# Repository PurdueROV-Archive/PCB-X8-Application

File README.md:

# PCB-X8-Application
The board that contains mission specific electronics

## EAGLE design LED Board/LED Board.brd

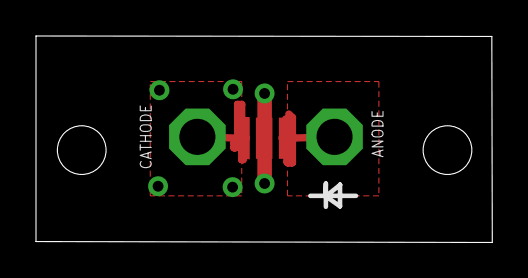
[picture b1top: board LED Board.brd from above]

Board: 2 copper layers, 25.3 x 11.5 mm, 3 parts (0 on the bottom side), 2 nets.

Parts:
ANODE: PTR1PAD1-20; P1-20
CATHODE: PTR1PAD1-20; P1-20
D1: CREE; CREE-XLAMP-XM-L

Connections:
CAM_LEDV: ANODE.TP, D1.A, D1.A@1
GND: CATHODE.TP, D1.C, D1.C1, D1.C@1

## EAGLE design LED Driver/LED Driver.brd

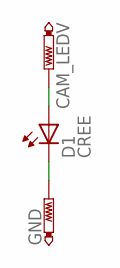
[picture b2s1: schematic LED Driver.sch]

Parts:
CAM_LEDV: PTR1PAD1-20; P1-20
D1: CREE; CREE-XLAMP-XM-L
GND: PTR1PAD1-20; P1-20

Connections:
CAM_LEDV: CAM_LEDV.TP, D1.A, D1.A@1 (A)
GND: D1.C, D1.C1 (C), D1.C@1 (C), GND.TP

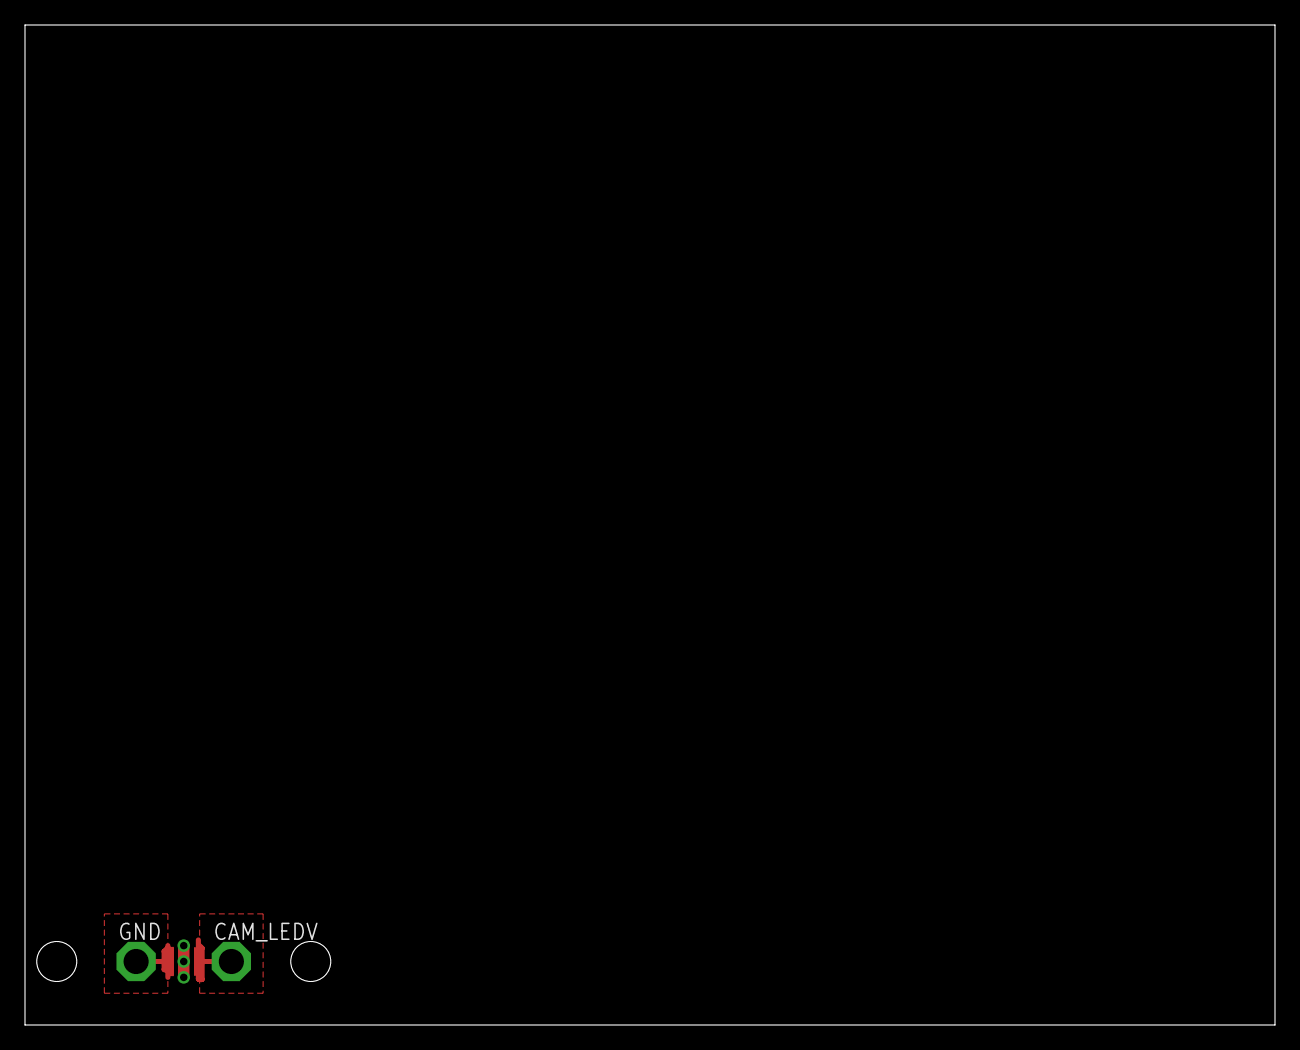
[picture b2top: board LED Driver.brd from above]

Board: 2 copper layers, 100.0 x 80.0 mm, 3 parts (0 on the bottom side), 2 nets.

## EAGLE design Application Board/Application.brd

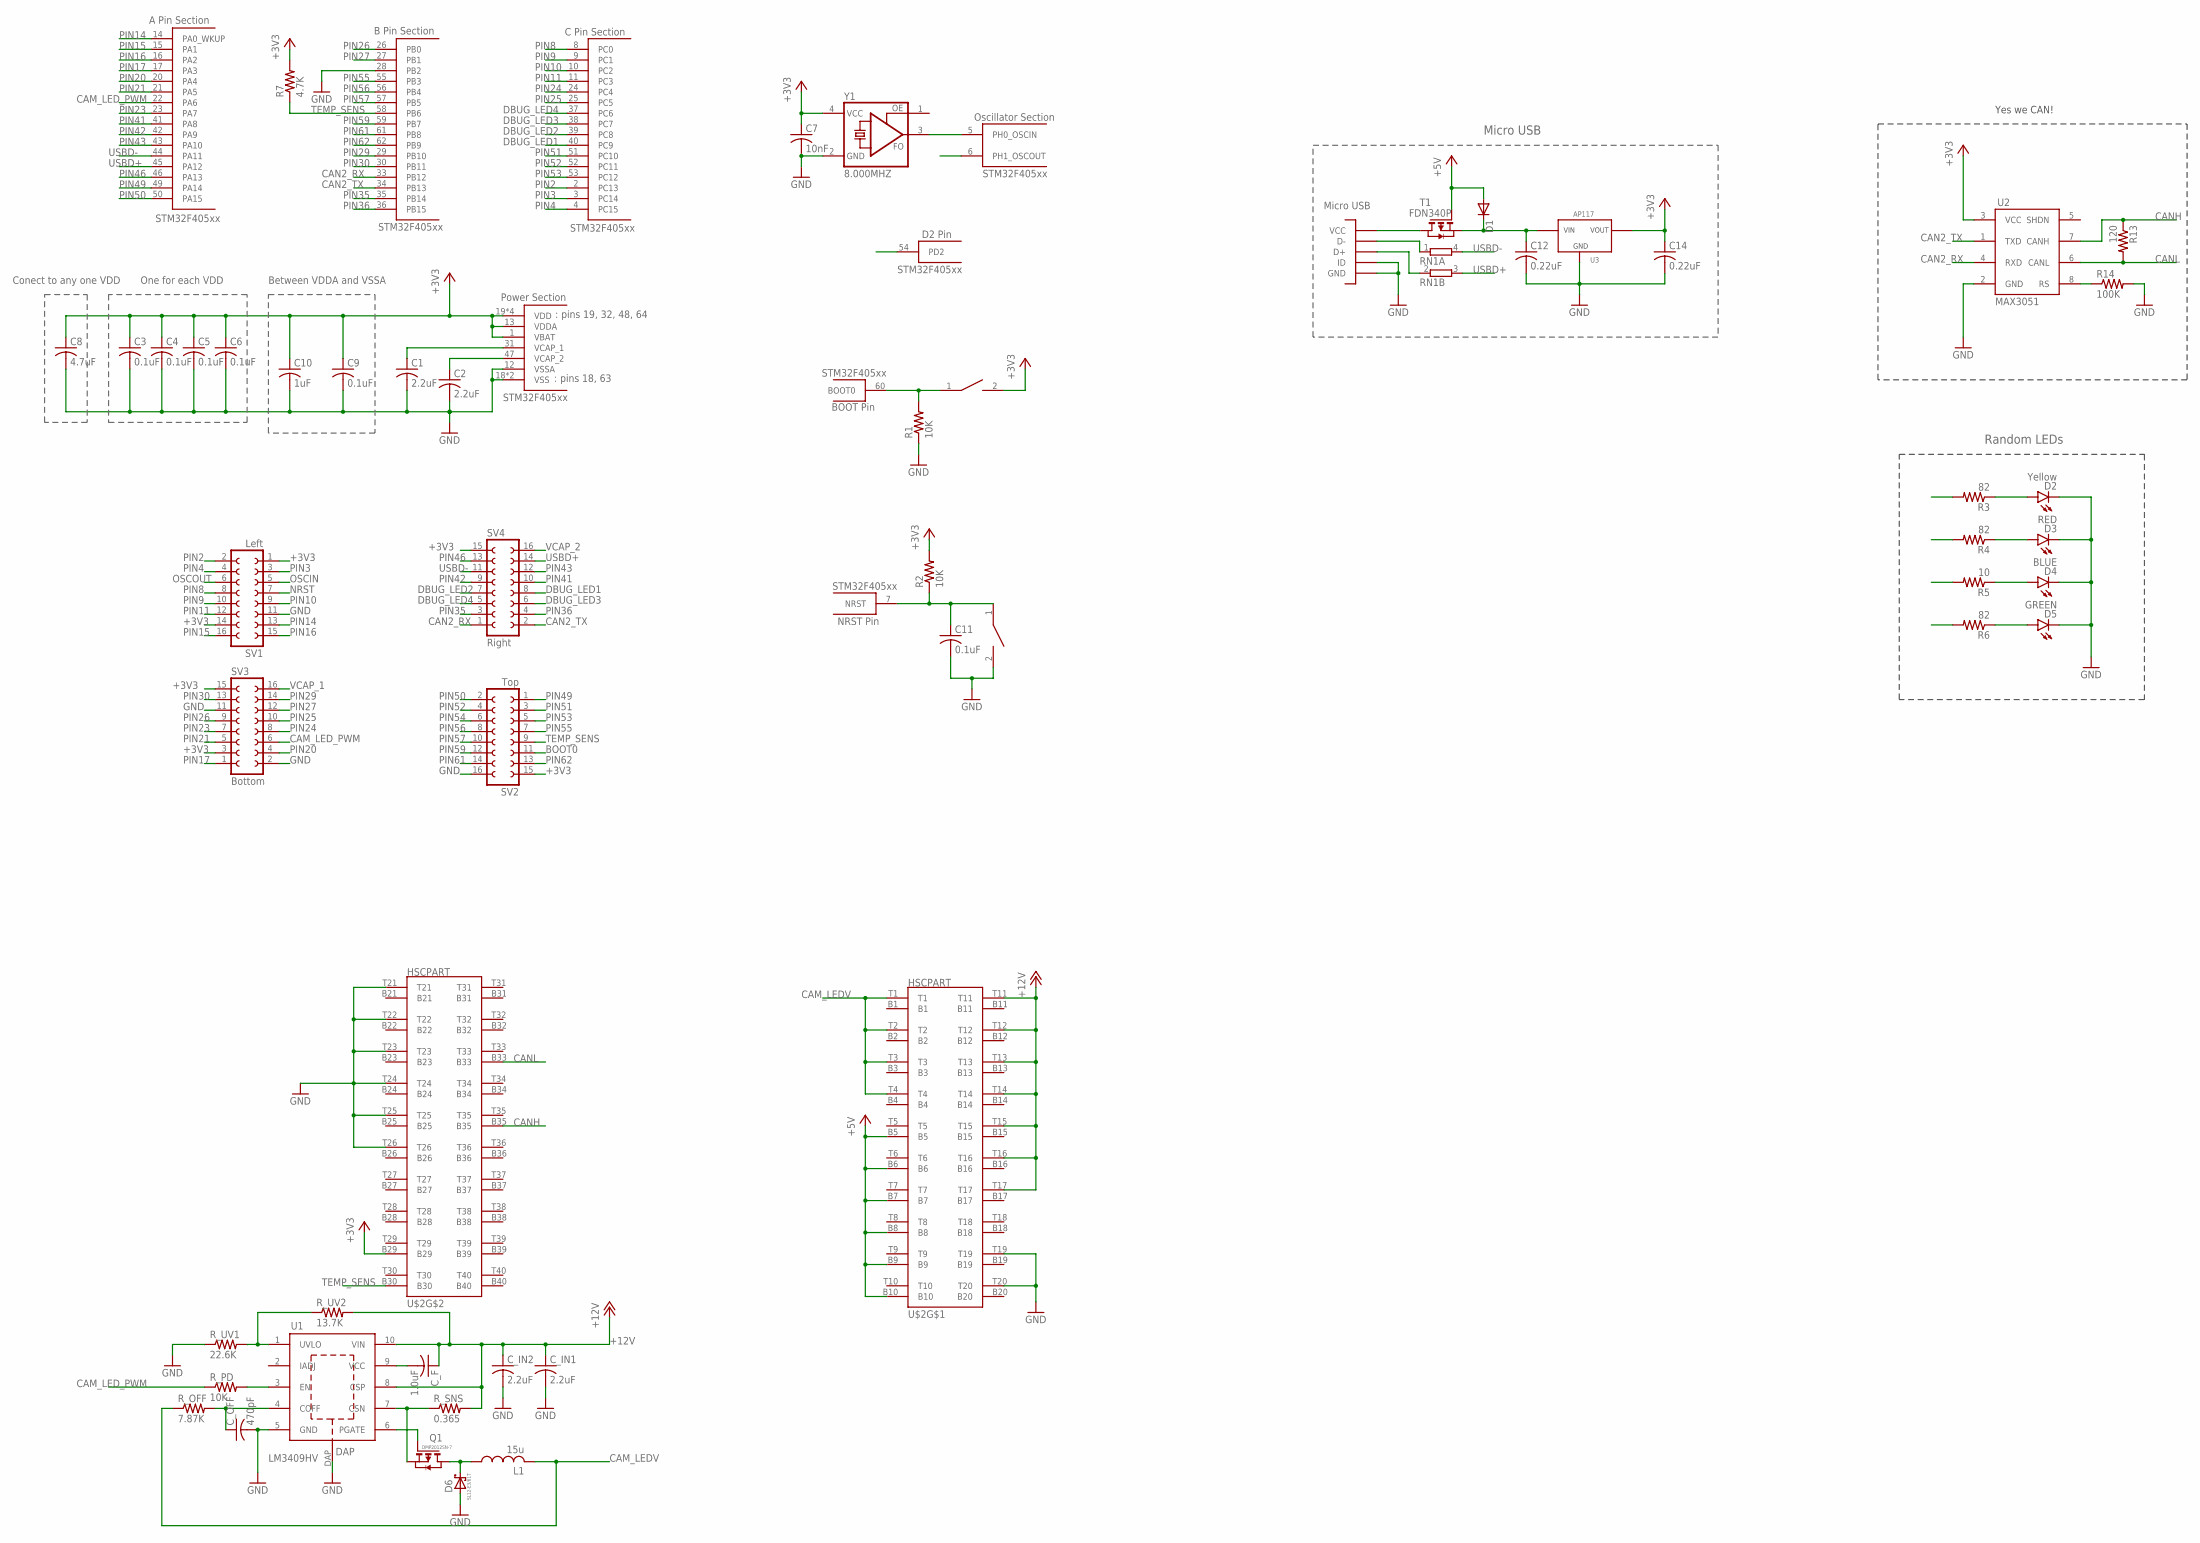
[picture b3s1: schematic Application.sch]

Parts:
C1, C2: 2.2uF; C0603
C3, C4, C5, C6, C9, C11: 0.1uF; C0603
C7: 10nF; C0603
C8: 4.7uF; C0603
C10: 1uF; C0603
C12, C14: 0.22uF; C0603
C_F: 1.0uF; C0603
C_IN1, C_IN2: 2.2uF; C0603
C_OFF: 470pF; C0603
D1: DIODE-DO-214AC; DO-214AC
D2: Yellow; LED-0603
D3: RED; LED-0603
D4: BLUE; LED-0603
D5: GREEN; LED-0603
D6: SL12-E3/61T
L1: 15u; SRN8040
Q1: DMP2012SN-7
R1, R2: 10K; R0603
R3, R4, R6: 82; R0603
R5: 10; R0603
R7: 4.7K; R0603
R13: 120; R0603
R14: 100K; R0603
RN1: 2R-NEXBV4V; EXBV4V
R_OFF: 7.87K; R0603
R_PD: 10K; R0603
R_SNS: 0.365; R2512
R_UV1: 22.6K; R0603
R_UV2: 13.7K; R0603
S1: BOOT; SW_2512
S2: RESET; SW_2512
SV1: Left; FE08-2
SV2: Top; FE08-2
SV3: Bottom; FE08-2
SV4: Right; FE08-2
T1: FDN340P; SOT-23
U1: LM3409HV; VSSOP-10
U2: MAX3051; SOT23-8L
U3: U3; SOT223
U$1: STM32F405; LQFP64
U$2: HSCPART; HSC8-40PINOUUT
U$4: MICROUSB; MICRO_B
Y1: 8.000MHZ; ASF

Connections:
+3V3: C3.1, C4.1, C5.1, C6.1, C7.1, C8.1, C9.1, C10.1, C14.1, R2.2, R7.2, S1.2, SV1.1, SV1.14, SV2.15, SV3.3, SV3.15, SV4.15, U2.3 (VCC), U3.TAB (VOUT), U3.VOUT, U$1.1 (VBAT), U$1.13 (VDDA), U$1.19 (VDD), U$1.32 (VDD), U$1.48 (VDD), U$1.64 (VDD), U$2.B29, Y1.4 (VCC)
+5V: D1.A, T1.3 (G), U$2.B5, U$2.B6, U$2.B7, U$2.B8, U$2.B9, U$2.B10
+12V: C_F.1, C_IN1.1, C_IN2.1, R_SNS.2, R_UV2.2, U1.8 (CSP), U1.10 (VIN), U$2.T11, U$2.T12, U$2.T13, U$2.T14, U$2.T15, U$2.T16, U$2.T17
BOOT0: R1.2, S1.1, SV2.11, U$1.60 (BOOT0)
CAM_LEDV: L1.2, R_OFF.1, U$2.T1, U$2.T2, U$2.T3, U$2.T4
CAM_LED_PWM: R_PD.1, SV3.6, U$1.22 (PA6)
CAN2_RX: SV4.1, U2.4 (RXD), U$1.33 (PB12)
CAN2_TX: SV4.2, U2.1 (TXD), U$1.34 (PB13)
CANH: R13.1, U2.7 (CANH), U$2.B35
CANL: R13.2, U2.6 (CANL), U$2.B33
DBUG_LED1: R3.2, SV4.8, U$1.40 (PC9)
DBUG_LED2: R4.2, SV4.7, U$1.39 (PC8)
DBUG_LED3: R5.2, SV4.6, U$1.38 (PC7)
DBUG_LED4: R6.2, SV4.5, U$1.37 (PC6)
GND: C1.2, C2.2, C3.2, C4.2, C5.2, C6.2, C7.2, C8.2, C9.2, C10.2, C11.2, C12.2, C14.2, C_IN1.2, C_IN2.2, C_OFF.2, D2.C, D3.C, D4.C, D5.C, D6.2 (A), R1.1, R14.2, R_UV1.1, S2.2, SV1.11, SV2.16, SV3.2, SV3.11, U1.5 (GND), U1.DAP, U2.2 (GND), U3.GND, U$1.12 (VSSA), U$1.18 (VSS), U$1.28 (PB2), U$1.63 (VSS), U$2.T19, U$2.T20, U$2.T21, U$2.T22, U$2.T23, U$2.T24, U$2.T25, U$2.T26, U$4.GND1 (GND), U$4.GND2 (GND), U$4.GND3 (GND), U$4.GND4 (GND), U$4.GND7 (GND), U$4.GND8 (GND), U$4.P4 (ID), U$4.P5 (GND), Y1.2 (GND)
L1: D6.1 (C), L1.1, Q1.1 (D)
unnamed: RN1.1, U$4.P2 (D-)
unnamed: R_UV1.2, R_UV2.1, U1.1 (UVLO)
unnamed: C_OFF.1, R_OFF.2, U1.4 (COFF)
unnamed: C_F.2, U1.9 (VCC)
unnamed: Q1.3 (S), R_SNS.1, U1.7 (CSN)
unnamed: R_PD.2, U1.3 (EN)
unnamed: Q1.2 (G), U1.6 (PGATE)
unnamed: RN1.2 (1), U$4.P3 (D+)
unnamed: T1.1 (D), U$4.P1 (VCC)
unnamed: C12.1, D1.C, T1.2 (S), U3.VIN
unnamed: D2.A, R3.1
unnamed: D3.A, R4.1
unnamed: D4.A, R5.1
unnamed: D5.A, R6.1
unnamed: R14.1, U2.8 (RS)
NRST: C11.1, R2.1, S2.1, SV1.7, U$1.7 (NRST)
OSCIN: SV1.5, U$1.5 (PH0_OSCIN), Y1.3 (FO)
OSCOUT: SV1.6, U$1.6 (PH1_OSCOUT)
PIN2: SV1.2, U$1.2 (PC13)
PIN3: SV1.3, U$1.3 (PC14)
PIN4: SV1.4, U$1.4 (PC15)
PIN8: SV1.8, U$1.8 (PC0)
PIN9: SV1.10, U$1.9 (PC1)
PIN10: SV1.9, U$1.10 (PC2)
PIN11: SV1.12, U$1.11 (PC3)
PIN14: SV1.13, U$1.14 (PA0_WKUP)
PIN15: SV1.16, U$1.15 (PA1)
PIN16: SV1.15, U$1.16 (PA2)
PIN17: SV3.1, U$1.17 (PA3)
PIN20: SV3.4, U$1.20 (PA4)
PIN21: SV3.5, U$1.21 (PA5)
PIN23: SV3.7, U$1.23 (PA7)
PIN24: SV3.8, U$1.24 (PC4)
PIN25: SV3.10, U$1.25 (PC5)
PIN26: SV3.9, U$1.26 (PB0)
PIN27: SV3.12, U$1.27 (PB1)
PIN29: SV3.14, U$1.29 (PB10)
PIN30: SV3.13, U$1.30 (PB11)
PIN35: SV4.3, U$1.35 (PB14)
PIN36: SV4.4, U$1.36 (PB15)
PIN41: SV4.10, U$1.41 (PA8)
PIN42: SV4.9, U$1.42 (PA9)
PIN43: SV4.12, U$1.43 (PA10)
PIN46: SV4.13, U$1.46 (PA13)
PIN49: SV2.1, U$1.49 (PA14)
PIN50: SV2.2, U$1.50 (PA15)
PIN51: SV2.3, U$1.51 (PC10)
PIN52: SV2.4, U$1.52 (PC11)
PIN53: SV2.5, U$1.53 (PC12)
PIN54: SV2.6, U$1.54 (PD2)
PIN55: SV2.7, U$1.55 (PB3)
PIN56: SV2.8, U$1.56 (PB4)
PIN57: SV2.10, U$1.57 (PB5)
PIN59: SV2.12, U$1.59 (PB7)
PIN61: SV2.14, U$1.61 (PB8)
PIN62: SV2.13, U$1.62 (PB9)
TEMP_SENS: R7.1, SV2.9, U$1.58 (PB6), U$2.B30
USBD+: RN1.3 (2), SV4.14, U$1.45 (PA12)
USBD-: RN1.4 (2), SV4.11, U$1.44 (PA11)
VCAP_1: C1.1, SV3.16, U$1.31 (VCAP_1)
VCAP_2: C2.1, SV4.16, U$1.47 (VCAP_2)

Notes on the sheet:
: pins 19, 32, 48, 64
: pins 18, 63
Between VDDA and VSSA
One for each VDD
Conect to any one VDD
Micro USB
Yes we CAN!
Random LEDs

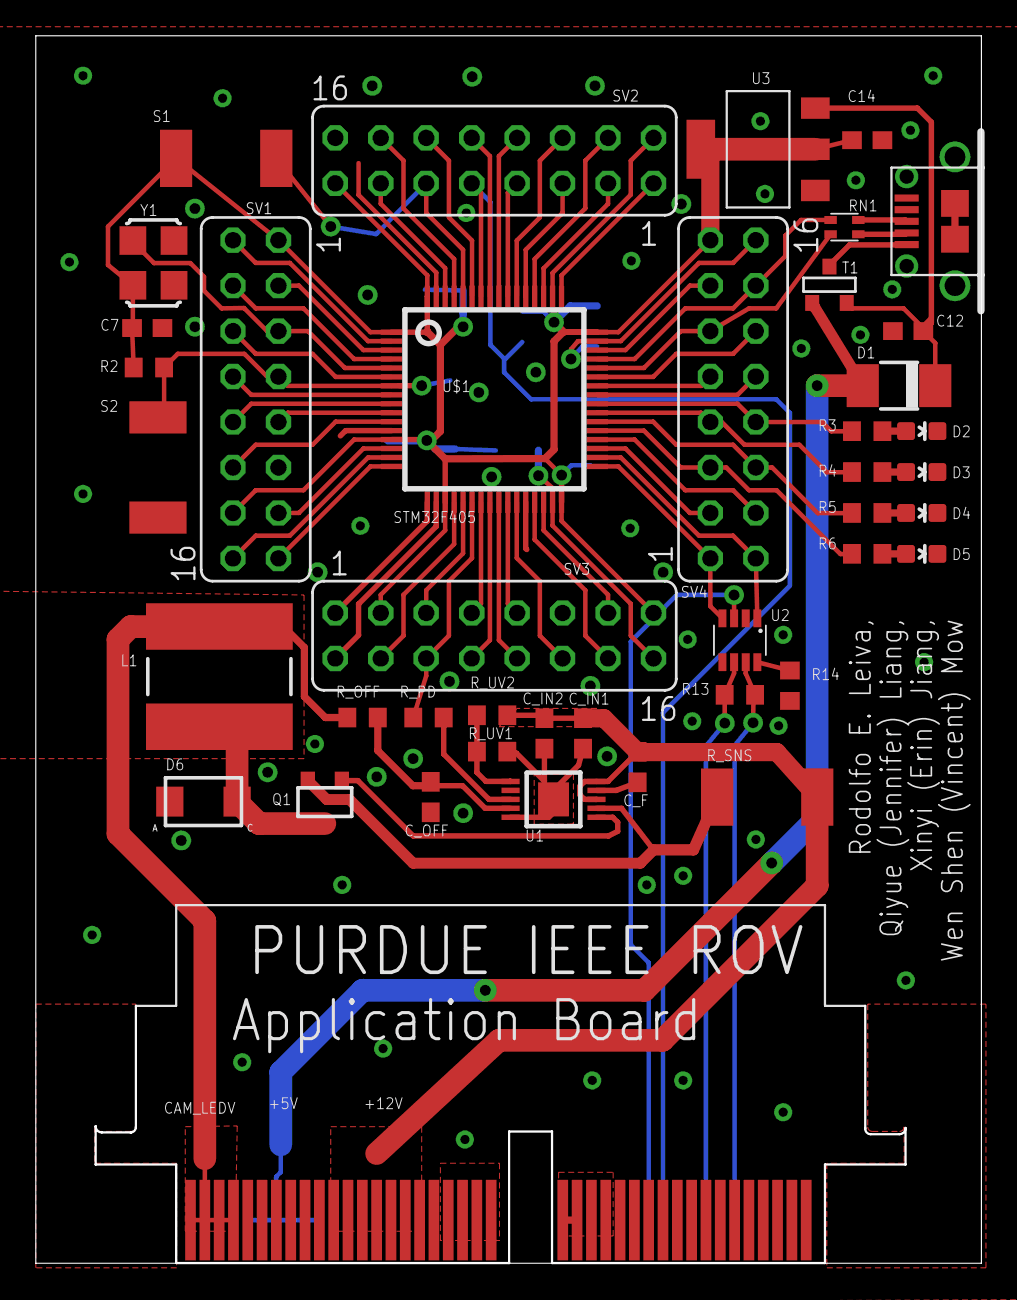
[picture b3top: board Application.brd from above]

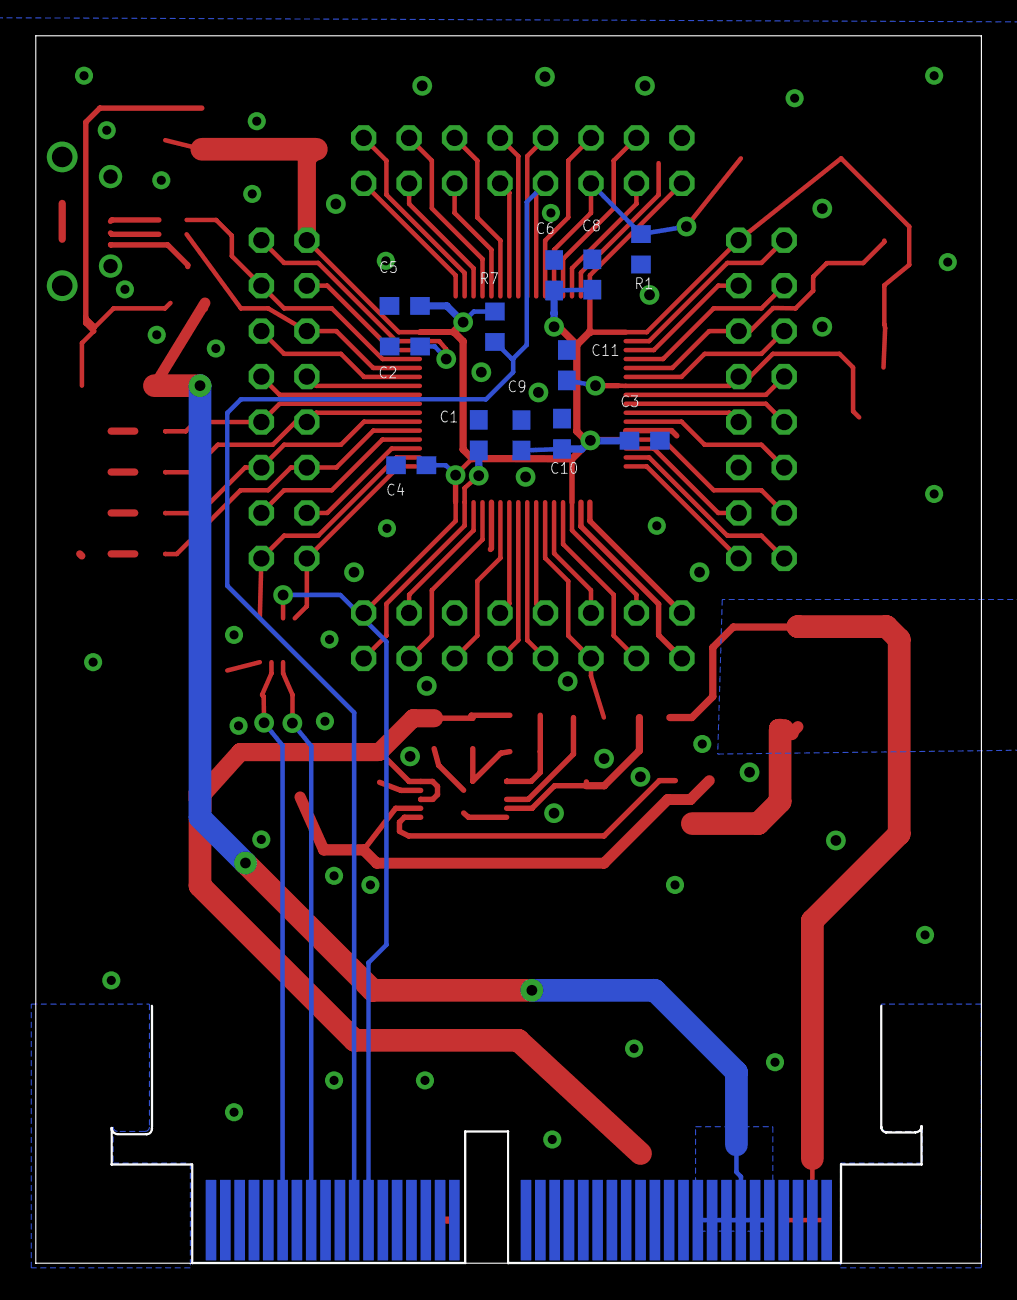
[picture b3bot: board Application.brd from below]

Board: 2 copper layers, 52.8 x 68.6 mm, 54 parts (12 on the bottom side), 77 nets.

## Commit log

2015-11-07 Added Can Schematic
    Can Schematic without CAN Controller
2015-11-07 Added CAN folder
2015-11-19 Added STM32F05 microcontroller shematic
    Not finished yet.
2015-11-19 Changes 11/18/2015
    Continued schematic design.
    Created PCB file
2015-11-21 Updated application micro board
2015-11-25 Continued work on application micro
    Added circuitry for bi-directional linear regulator. Named some pins.
2015-11-25 Added last parts to application board microcontroller.
    Added the linear regulator, finished as much of schematic as we can for
    now. *I think* Now all that's left is deciding what pins do what.
2015-12-02 Connected the programming pins
2015-12-03 LED Drivers (Buck Converter)
    Here are two different board layouts for the buck converter. The first
    version was done without any consideration for proper buck converter PCB
    design. The second version takes into account design recommendations as
    specified in:
    http://rohmfs.rohm.com/en/products/databook/applinote/ic/power/switching_regulator/converter_pcb_layout_appli-e.pdf
    and http://cds.linear.com/docs/en/application-note/an136f.pdf. However
2015-12-05 Minor changes to trace placement in LED Driver v2
    Minor changes to trace placement in LED Driver v2
2015-12-05 Added README
2015-12-05 Updated LED Driver README
2015-12-05 Updated LED driver README
    Added component land pattern considerations
2015-12-05 Added the LED driver PPT
    Used for the design review
2015-12-05 Made LED Driver v1 obsolete
    Refer to LED Driver v2 instead
2015-12-05 Minor trace adjustments
    Adjustments updated to eagle board file and powerpoint file
2015-12-05 Application Micro V2
    Removed shift regulator (for I2C), named pins, connected can circuit to
    can schematic.
2015-12-07 Changes to traces and fills
    Changed non-thermal fills to thermals/traces for most non-power
    components. Main trace sizes used to route those components are 0.025"
    and 0.012"
2015-12-10 change the value of LED resistors
2015-12-10 Started Routing
2015-12-10 combined application board parts into one board
2015-12-28 Fixed some bad git practices
2015-12-31 Moved capacitors around
2015-12-31 Fixed all the routing on the microcontroller.
2015-12-31 added order of board input voltage and signals
2016-01-01 Rearranged components, including LED driver.
    Not finished, still need to fix LED driver and route the remaining
    connector lines.
2016-01-07 updated stm... microcontroller to the updated version
    organized order of output lines. Still not complete.
2016-01-07 Fixed output voltages and signal paths, added connector
2016-01-08 Fixed up some wiring
2016-01-08 fixed some connections
    Have been trying to solve some problems with some polygons and haven't
    been able to fix other issues.
2016-01-09 fixed ground planes and added vias
2016-01-09 update 1/8/2016
    cant remember what I changed. What ever it was must have been minor.
    looks like a change in via position and sizes and a few other minor
    adjustments.
2016-01-09 Cleaned up some of the traces
2016-01-14 Added The U Type +3V3 Wire
2016-01-15 got rid of the lock files
    I hate ".lck". I don't know what to do with them or how they are helpful
    to me.
2016-01-15 Update 1/15/16 4:50pm
    Added Temp_Sens Pullup Resistor, connected remaining air wires, modified
    path of a few lines
2016-01-15 Fixed some DLC Errors
2016-01-16 Fixed some DRC errors?
2016-01-16 Fixed All The DRC Errors Except The Dimension Errors
2016-01-16 Board Layout Finished！
2016-01-16 Added Designers names and "PURDUE IEEE ROV"
2016-01-16 Changed some names, added vias
2016-01-16 Added Gerber Files and Designers Aliases
2016-02-27 Update on changes since last push
    Can't remember everything I changed, but it was mostly reorganizing
    names.
2016-02-27 Created LED Driver
2016-03-04 board sketch up model update
2016-03-23 Updated LED board
    Ready for manufacturing
2016-04-02 Added symbols to the LED board
2016-04-03 Fixed dimensions of LED board
    Also added measurement documentation on board.
    Included png file of final board with measurements.
2016-05-04 I don't know what got updated

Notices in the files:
parts and their libraries:
SparkFun-LED: Licensing: Creative Commons ShareAlike 4.0 International - https://creativecommons.org/licenses/by-sa/4.0
